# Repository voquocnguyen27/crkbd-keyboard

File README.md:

# crkbd-keyboard
My clone of Corne Keyboard using Arduino Pro Micro

# About this project
This project was created because of my love for split keyboards, my desire to try it out but I don't have the conditions to meet the price offered by the manufacturer.
# Skills
This project is based on basic knowledge of electronic circuits, micro controllers, circuit making techniques and programming skills for micro controllers.
# Tools
Schematic and PCB was created in KiCAD with the external library provided by Joe Scotto. 
He is the one who inspired me to create my own keyboard and also provided me with a lot of useful knowledge and guidance for implementing my own project.
You can find his Youtube channel here:
```bash
https://www.youtube.com/@joe_scotto
```

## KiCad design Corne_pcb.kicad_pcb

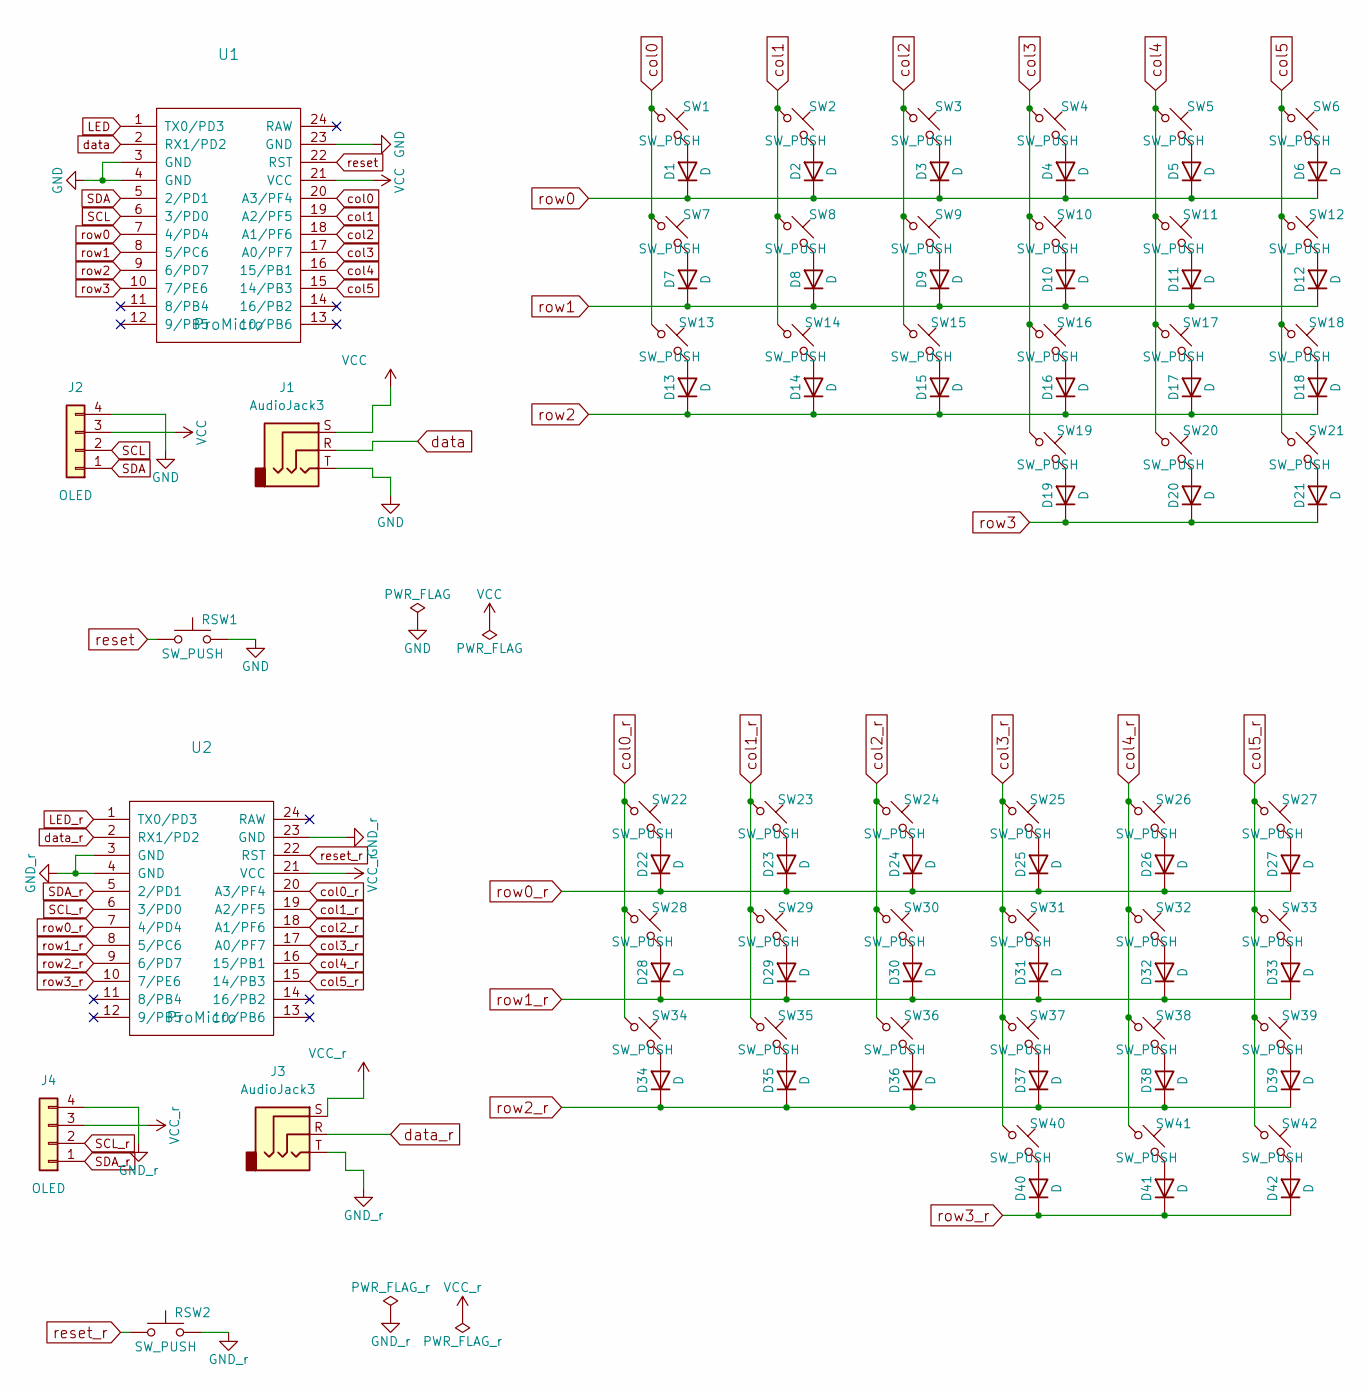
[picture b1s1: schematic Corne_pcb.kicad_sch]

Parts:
D1, D2, D3, D4, D5, D6, D7, D8, D9, D10, D11, D12, D13, D14, D15, D16, D17, D18, D19, D20, D21, D22, D23, D24, D25, D26, D27, D28, D29, D30, D31, D32, D33, D34, D35, D36, D37, D38, D39, D40, D41, D42: D; D_DO-35_SOD27_P7.62mm_Horizontal
J1, J3: AudioJack3; Jack_3.5mm_CUI_SJ1-3525N_Horizontal
J2, J4: OLED; OLED_128x32
RSW1, RSW2: SW_PUSH; SW_PUSH_1P1T_6x3.5mm_H4.3_APEM_MJTP1243
SW1, SW2, SW3, SW4, SW5, SW6, SW7, SW8, SW9, SW10, SW11, SW12, SW13, SW14, SW15, SW16, SW17, SW18, SW19, SW20, SW21, SW22, SW23, SW24, SW25, SW26, SW27, SW28, SW29, SW30, SW31, SW32, SW33, SW34, SW35, SW36, SW37, SW38, SW39, SW40, SW41, SW42: SW_PUSH; Hotswap_MX_1.00u
U1, U2: ProMicro; Arduino_Pro_Micro

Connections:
GND: J1.T, J2.4, RSW1.2, U1.3 (GND), U1.4 (GND), U1.23 (GND)
GND_r: J3.T, J4.4, RSW2.2, U2.3 (GND), U2.4 (GND), U2.23 (GND)
LED: U1.1 (TX0/PD3)
LED_r: U2.1 (TX0/PD3)
unnamed: D1.2 (A), SW1.2
unnamed: D2.2 (A), SW2.2
unnamed: D3.2 (A), SW3.2
unnamed: D4.2 (A), SW4.2
unnamed: D5.2 (A), SW5.2
unnamed: D6.2 (A), SW6.2
unnamed: D7.2 (A), SW7.2
unnamed: D8.2 (A), SW8.2
unnamed: D9.2 (A), SW9.2
unnamed: D10.2 (A), SW10.2
unnamed: D11.2 (A), SW11.2
unnamed: D12.2 (A), SW12.2
unnamed: D13.2 (A), SW13.2
unnamed: D14.2 (A), SW14.2
unnamed: D15.2 (A), SW15.2
unnamed: D16.2 (A), SW16.2
unnamed: D17.2 (A), SW17.2
unnamed: D18.2 (A), SW18.2
unnamed: D19.2 (A), SW19.2
unnamed: D20.2 (A), SW20.2
unnamed: D21.2 (A), SW21.2
unnamed: D22.2 (A), SW22.2
unnamed: D23.2 (A), SW23.2
unnamed: D24.2 (A), SW24.2
unnamed: D25.2 (A), SW25.2
unnamed: D26.2 (A), SW26.2
unnamed: D27.2 (A), SW27.2
unnamed: D28.2 (A), SW28.2
unnamed: D29.2 (A), SW29.2
unnamed: D30.2 (A), SW30.2
unnamed: D31.2 (A), SW31.2
unnamed: D32.2 (A), SW32.2
unnamed: D33.2 (A), SW33.2
unnamed: D34.2 (A), SW34.2
unnamed: D35.2 (A), SW35.2
unnamed: D36.2 (A), SW36.2
unnamed: D37.2 (A), SW37.2
unnamed: D38.2 (A), SW38.2
unnamed: D39.2 (A), SW39.2
unnamed: D40.2 (A), SW40.2
unnamed: D41.2 (A), SW41.2
unnamed: D42.2 (A), SW42.2
SCL: J2.2, U1.6 (3/PD0)
SCL_r: J4.2, U2.6 (3/PD0)
SDA: J2.1, U1.5 (2/PD1)
SDA_r: J4.1, U2.5 (2/PD1)
VCC: J1.S, J2.3, U1.21 (VCC)
VCC_r: J3.S, J4.3, U2.21 (VCC)
col0: SW1.1, SW7.1, SW13.1, U1.20 (A3/PF4)
col0_r: SW22.1, SW28.1, SW34.1, U2.20 (A3/PF4)
col1: SW2.1, SW8.1, SW14.1, U1.19 (A2/PF5)
col1_r: SW23.1, SW29.1, SW35.1, U2.19 (A2/PF5)
col2: SW3.1, SW9.1, SW15.1, U1.18 (A1/PF6)
col2_r: SW24.1, SW30.1, SW36.1, U2.18 (A1/PF6)
col3: SW4.1, SW10.1, SW16.1, SW19.1, U1.17 (A0/PF7)
col3_r: SW25.1, SW31.1, SW37.1, SW40.1, U2.17 (A0/PF7)
col4: SW5.1, SW11.1, SW17.1, SW20.1, U1.16 (15/PB1)
col4_r: SW26.1, SW32.1, SW38.1, SW41.1, U2.16 (15/PB1)
col5: SW6.1, SW12.1, SW18.1, SW21.1, U1.15 (14/PB3)
col5_r: SW27.1, SW33.1, SW39.1, SW42.1, U2.15 (14/PB3)
data: J1.R, U1.2 (RX1/PD2)
data_r: J3.R, U2.2 (RX1/PD2)
reset: RSW1.1, U1.22 (RST)
reset_r: RSW2.1, U2.22 (RST)
row0: D1.1 (K), D2.1 (K), D3.1 (K), D4.1 (K), D5.1 (K), D6.1 (K), U1.7 (4/PD4)
row0_r: D22.1 (K), D23.1 (K), D24.1 (K), D25.1 (K), D26.1 (K), D27.1 (K), U2.7 (4/PD4)
row1: D7.1 (K), D8.1 (K), D9.1 (K), D10.1 (K), D11.1 (K), D12.1 (K), U1.8 (5/PC6)
row1_r: D28.1 (K), D29.1 (K), D30.1 (K), D31.1 (K), D32.1 (K), D33.1 (K), U2.8 (5/PC6)
row2: D13.1 (K), D14.1 (K), D15.1 (K), D16.1 (K), D17.1 (K), D18.1 (K), U1.9 (6/PD7)
row2_r: D34.1 (K), D35.1 (K), D36.1 (K), D37.1 (K), D38.1 (K), D39.1 (K), U2.9 (6/PD7)
row3: D19.1 (K), D20.1 (K), D21.1 (K), U1.10 (7/PE6)
row3_r: D40.1 (K), D41.1 (K), D42.1 (K), U2.10 (7/PE6)

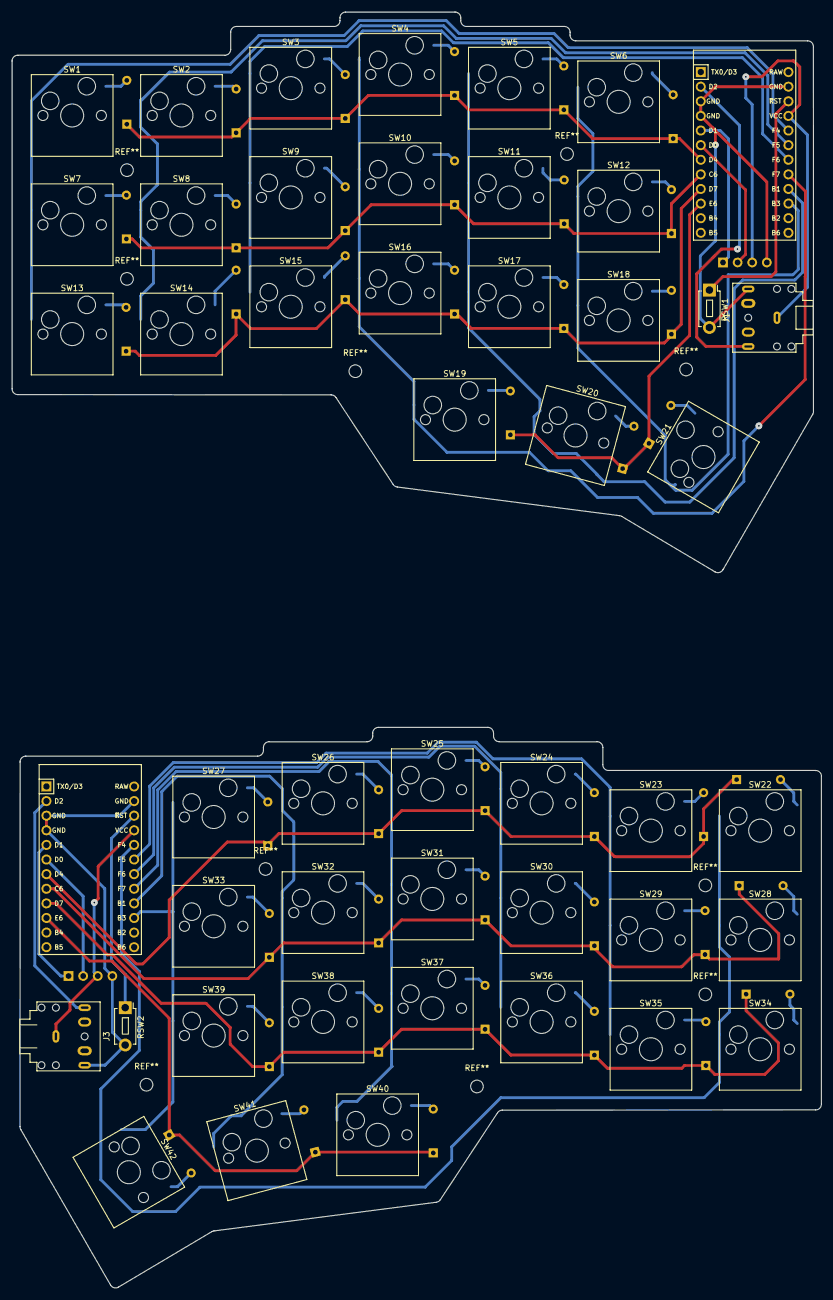
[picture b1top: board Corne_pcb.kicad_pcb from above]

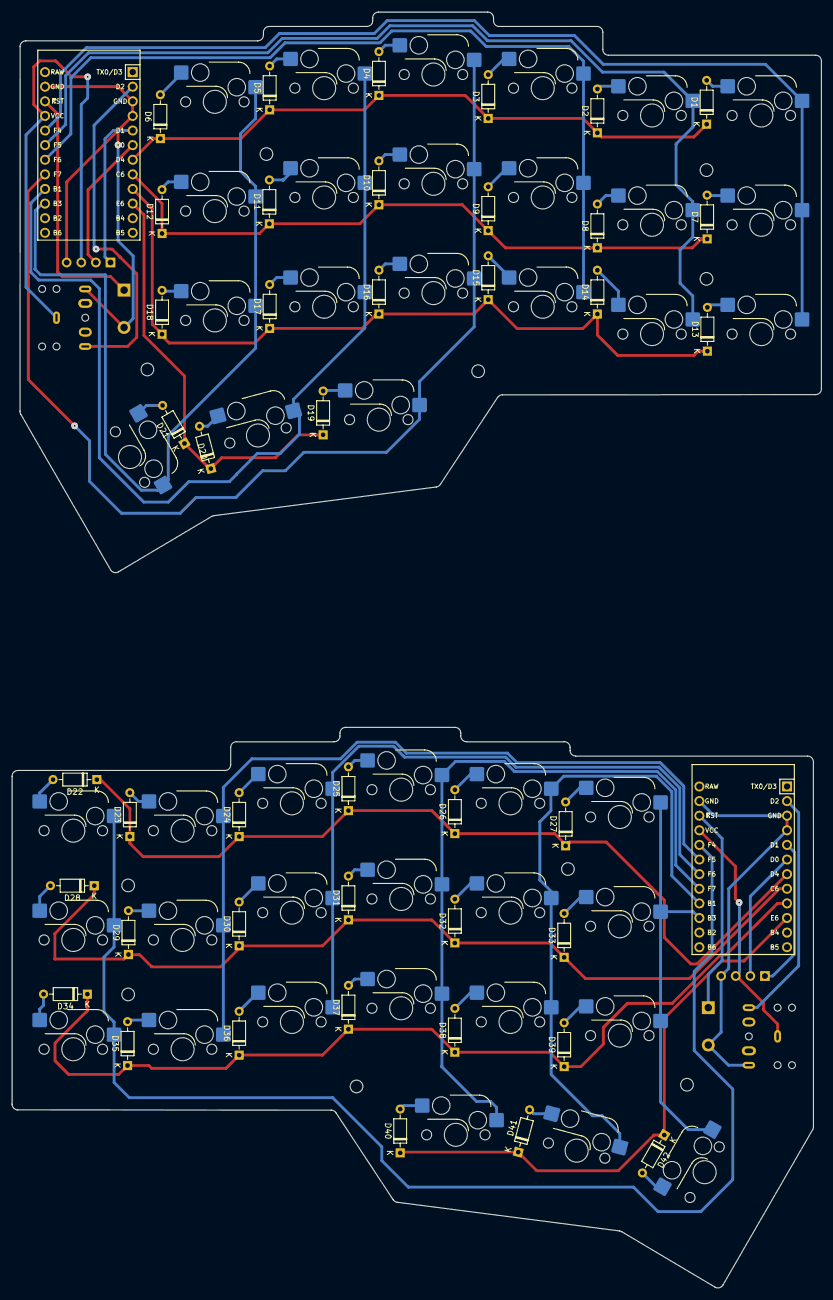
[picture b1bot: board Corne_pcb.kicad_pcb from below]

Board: 2 copper layers, 140.7 x 221.8 mm, 92 parts (44 on the bottom side), 74 nets.

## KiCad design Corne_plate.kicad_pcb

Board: 2 copper layers, 42 parts (0 on the bottom side), 12 nets, no tracks yet.

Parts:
SW1, SW2, SW3, SW4, SW5, SW6, SW7, SW8, SW9, SW10, SW11, SW12, SW13, SW14, SW15, SW16, SW17, SW18, SW19, SW20, SW21, SW22, SW23, SW24, SW25, SW26, SW27, SW28, SW29, SW30, SW31, SW32, SW33, SW34, SW35, SW36, SW37, SW38, SW39, SW40, SW41, SW42: SW_PUSH; Hotswap_MX_1.00u

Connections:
col0: SW1.1, SW7.1, SW13.1
col0_r: SW22.1, SW28.1, SW34.1
col1: SW2.1, SW8.1, SW14.1
col1_r: SW23.1, SW29.1, SW35.1
col2: SW3.1, SW9.1, SW15.1
col2_r: SW24.1, SW30.1, SW36.1
col3: SW4.1, SW10.1, SW16.1, SW19.1
col3_r: SW25.1, SW31.1, SW37.1, SW40.1
col4: SW5.1, SW11.1, SW17.1, SW20.1
col4_r: SW26.1, SW32.1, SW38.1, SW41.1
col5: SW6.1, SW12.1, SW18.1, SW21.1
col5_r: SW27.1, SW33.1, SW39.1, SW42.1
